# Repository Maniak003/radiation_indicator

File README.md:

<!DOCTYPE html>
<html lang="en" data-color-mode="auto" data-light-theme="light" data-dark-theme="dark">
  <head>
    <meta charset="utf-8">
  </head>
    <body class="logged-in env-production page-responsive page-blob" style="word-wrap: break-word;">
      <p> Radiation indicator. (The device is under development.)</p>
      
    </body>
</html>

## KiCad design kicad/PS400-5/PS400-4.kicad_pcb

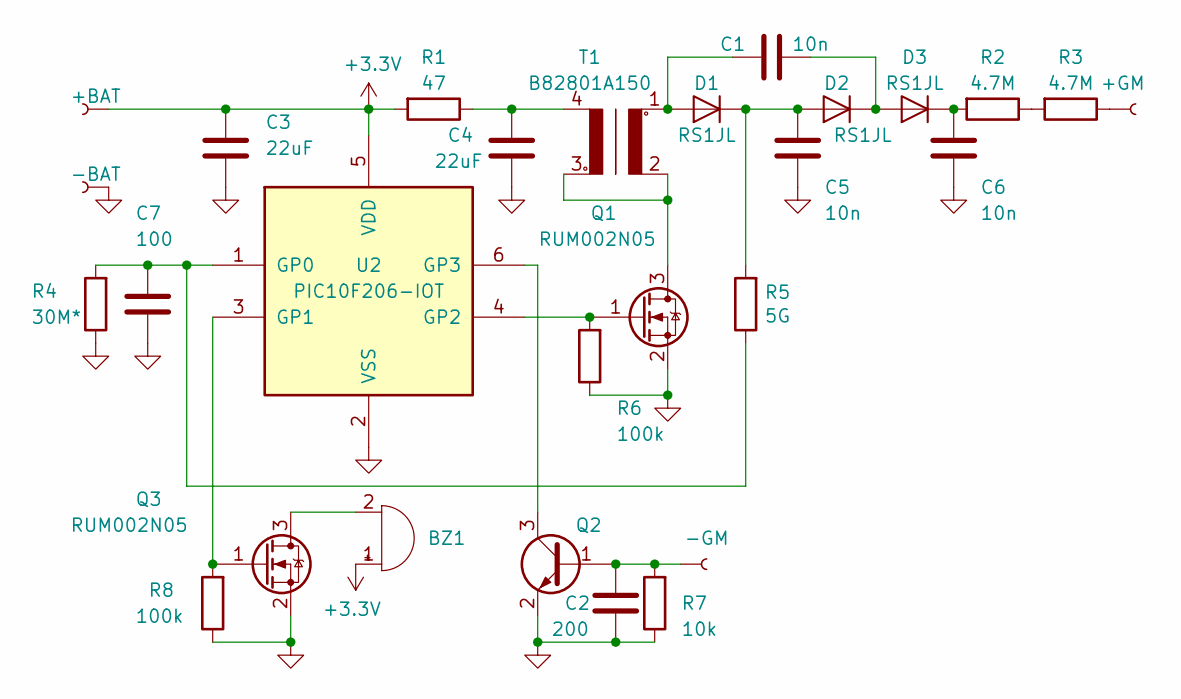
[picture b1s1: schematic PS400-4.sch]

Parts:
BZ1: Buzzer; BuzerSMD
C1, C5, C6: 10n; C_1812_4532Metric
C2: 200; C_0402_1005Metric
C3, C4: 22uF; C_0805_2012Metric
C7: 100; C_0402_1005Metric
D1, D2, D3: RS1JL; D_SOD-123
J1: +BAT; SMD-CONN
J2: +GM; SMD-CONN
J3: -BAT; SMD-CONN
J4: -GM; SMD-CONN
Q1, Q3: RUM002N05; SOT-723
Q2: Q_NPN_BEC; SOT-23
R1: 47; R_0402_1005Metric
R2, R3: 4.7M; R_0603_1608Metric
R4: 30M*; R_0402_1005Metric
R5: 5G; R_1210_3225Metric
R6, R8: 100k; R_0402_1005Metric
R7: 10k; R_0402_1005Metric
T1: B82801A150; B82801A1
U2: PIC10F206-IOT; SOT-23-6

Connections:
+3V3: BZ1.1 (-), C3.1, J1.1, R1.2, U2.5 (VDD)
GND: C2.2, C3.2, C4.2, C5.2, C6.2, C7.2, J3.1, Q1.2 (S), Q2.2 (E), Q3.2 (S), R4.1, R6.1, R7.1, R8.1, U2.2 (VSS)
unnamed: BZ1.2 (+), Q3.3 (D)
unnamed: C1.1, D2.1 (K), D3.2 (A)
unnamed: C1.2, D1.2 (A), T1.1
unnamed: C2.1, J4.1, Q2.1 (B), R7.2
unnamed: C4.1, R1.1, T1.4
unnamed: C5.1, D1.1 (K), D2.2 (A), R5.2
unnamed: C6.1, D3.1 (K), R2.2
unnamed: C7.1, R4.2, R5.1, U2.1 (GP0)
unnamed: J2.1, R3.1
unnamed: Q1.1 (G), R6.2, U2.4 (GP2)
unnamed: Q1.3 (D), T1.2, T1.3
unnamed: Q2.3 (C), U2.6 (GP3)
unnamed: Q3.1 (G), R8.2, U2.3 (GP1)
unnamed: R2.1, R3.2

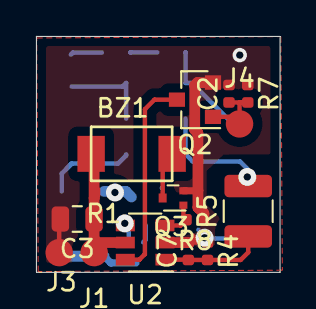
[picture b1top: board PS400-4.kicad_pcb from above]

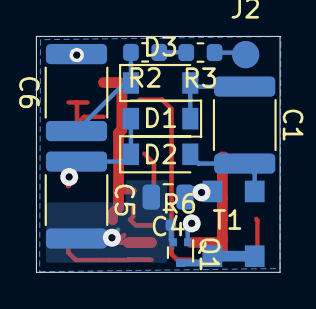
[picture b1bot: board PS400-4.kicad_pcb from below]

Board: 2 copper layers, 13.5 x 13.1 mm, 28 parts (13 on the bottom side), 16 nets.

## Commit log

2022-04-05 новый файл: kicad/PS400-5/PS400-4 новый файл: kicad/PS400-5/PS400-4-cache.lib новый файл: kicad/PS400-5/PS400-4-rescue.dcm новый файл: kicad/PS400-5/PS400-4-rescue.lib новый файл: kicad/PS400-5/PS400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
2022-04-05 новый файл: Documents/circuit.png изменено: README.md изменено: kicad/PS400-5/PS400-4.pdf
2022-04-06 изменено: Documents/circuit.png изменено: kicad/PS400-5/PS400-4.kicad_pcb изменено: kicad/PS400-5/PS400-4.kicad_pcb-bak изменено: kicad/PS400-5/PS400-4.pdf изменено: kicad/PS400-5/PS400-4.sch изменен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
2022-04-06 изменено: Documents/circuit.png изменено: kicad/PS400-5/PS400-4-cache.lib изменено: kicad/PS400-5/PS400-4.kicad_pcb изменено: kicad/PS400-5/PS400-4.kicad_pcb-bak изменено: kicad/PS400-5/PS400-4.pdf и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
2022-04-06 изменено: kicad/PS400-5/PS400-4.pdf изменено: kicad/PS400-5/PS400-4.sch изменено: kicad/PS400-5/PS400-4.sch-bak
2022-04-06 изменено: Documents/circuit.png
2022-04-07 изменено: kicad/PS400-5/PS400-4.kicad_pcb изменено: kicad/PS400-5/PS400-4.kicad_pcb-bak изменено: kicad/PS400-5/fp-info-cache
2022-04-10 новый файл: mplab/Makefile новый файл: mplab/build/default/debug/newmain.p1 новый файл: mplab/build/default/debug/newmain.p1.d новый файл: mplab/build/default/debug/newmain.pre новый файл: mplab/buil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
